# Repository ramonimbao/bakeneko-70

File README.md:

# Bakeneko 70 V1

A 70% keyboard based on the Bakeneko 60 by kkatano.

## Notes

Since this was based off of the Bakeneko 60, please take note that some files might still be named as bakeneko-60 or such. 

## Layouts

---

# Bakeneko 60 V3

A simple 60% keyboard for DIYers. This project is a special homage to TGR x Singa UNIKORN 60 and OTD 356 Mini.

## Features

- Single piece tray case
- O-ring gasket mount (Friction fit)
- USB-C with [Unified Daughterboard](https://github.com/ai03-2725/Unified-Daughterboard)
- QMK firmware and VIA ready
- Compatible with common 60% plates

## Specs

- Dimensions: 295 x 110 x 30mm
- Front height: 18.5mm
- Home row height: 31mm(with GMK keycaps and bumpons)
- Typing angle: 6 degree
- Weight:
  - PLA Case: 370g
  - Aluminum Case: 700g
- O-ring gasket: VMQ-50(Silicone 50 duro) AS568-262

## Notes

- All files are to be used at your own risk
- As for stabilizers, only PCB snap ins are supported
- This open source version is not compatible with CannonKeys' Bakeneko

## Resources

- Documents: https://drive.google.com/drive/folders/1tddSihOS8Pgf1lTQOjHohYCl8efxXIeH
  - Parts guide and other useful information
  - Will be added and updated as needed
- Discord: https://discord.gg/fMY96TeEwV
  - Have fun with community members
  - Talk about Bakeneko builds and mods, and share your works
  - You can also contact me from there

## Special thanks to

- **Elaine** for [Unikorn](https://geekhack.org/index.php?topic=98587.50). Allowed me to publish the Unikorn-inspired case as open source and encouraged me
- Of course, I also show my respect and gratitude to **yuktsi**
- **coarse** for PCB review and kind support. His great work has refined the PCB well

## Also I should mention

- **OTD** for 356 Mini. Origin of O-ring gasket mount style
- **Evy** for [Plain60 series](https://github.com/evyd13/plain60-c). I used it as a reference for my PCB design. They also answered my miscellaneous questions
- **ai03** for [MX_Alps_Hybrid](https://github.com/ai03-2725/MX_Alps_Hybrid) and [random-keyboard-parts.pretty](https://github.com/ai03-2725/random-keyboard-parts.pretty). Also got a lot of help from his discord server
- **overset** for [JP01](https://github.com/overset/JP01). The idea of publishing the case design on Onshape. After seeing their great work I switched from fusion360 to Onshape
- **Rhuk** gave me a lot of advice on keyboard design and manufacturing
- **Maker Keyboards** suggested adding a plate cutout to remove the PCB using a keycap puller
- And many community members for giving me advice and feedback, thanks!

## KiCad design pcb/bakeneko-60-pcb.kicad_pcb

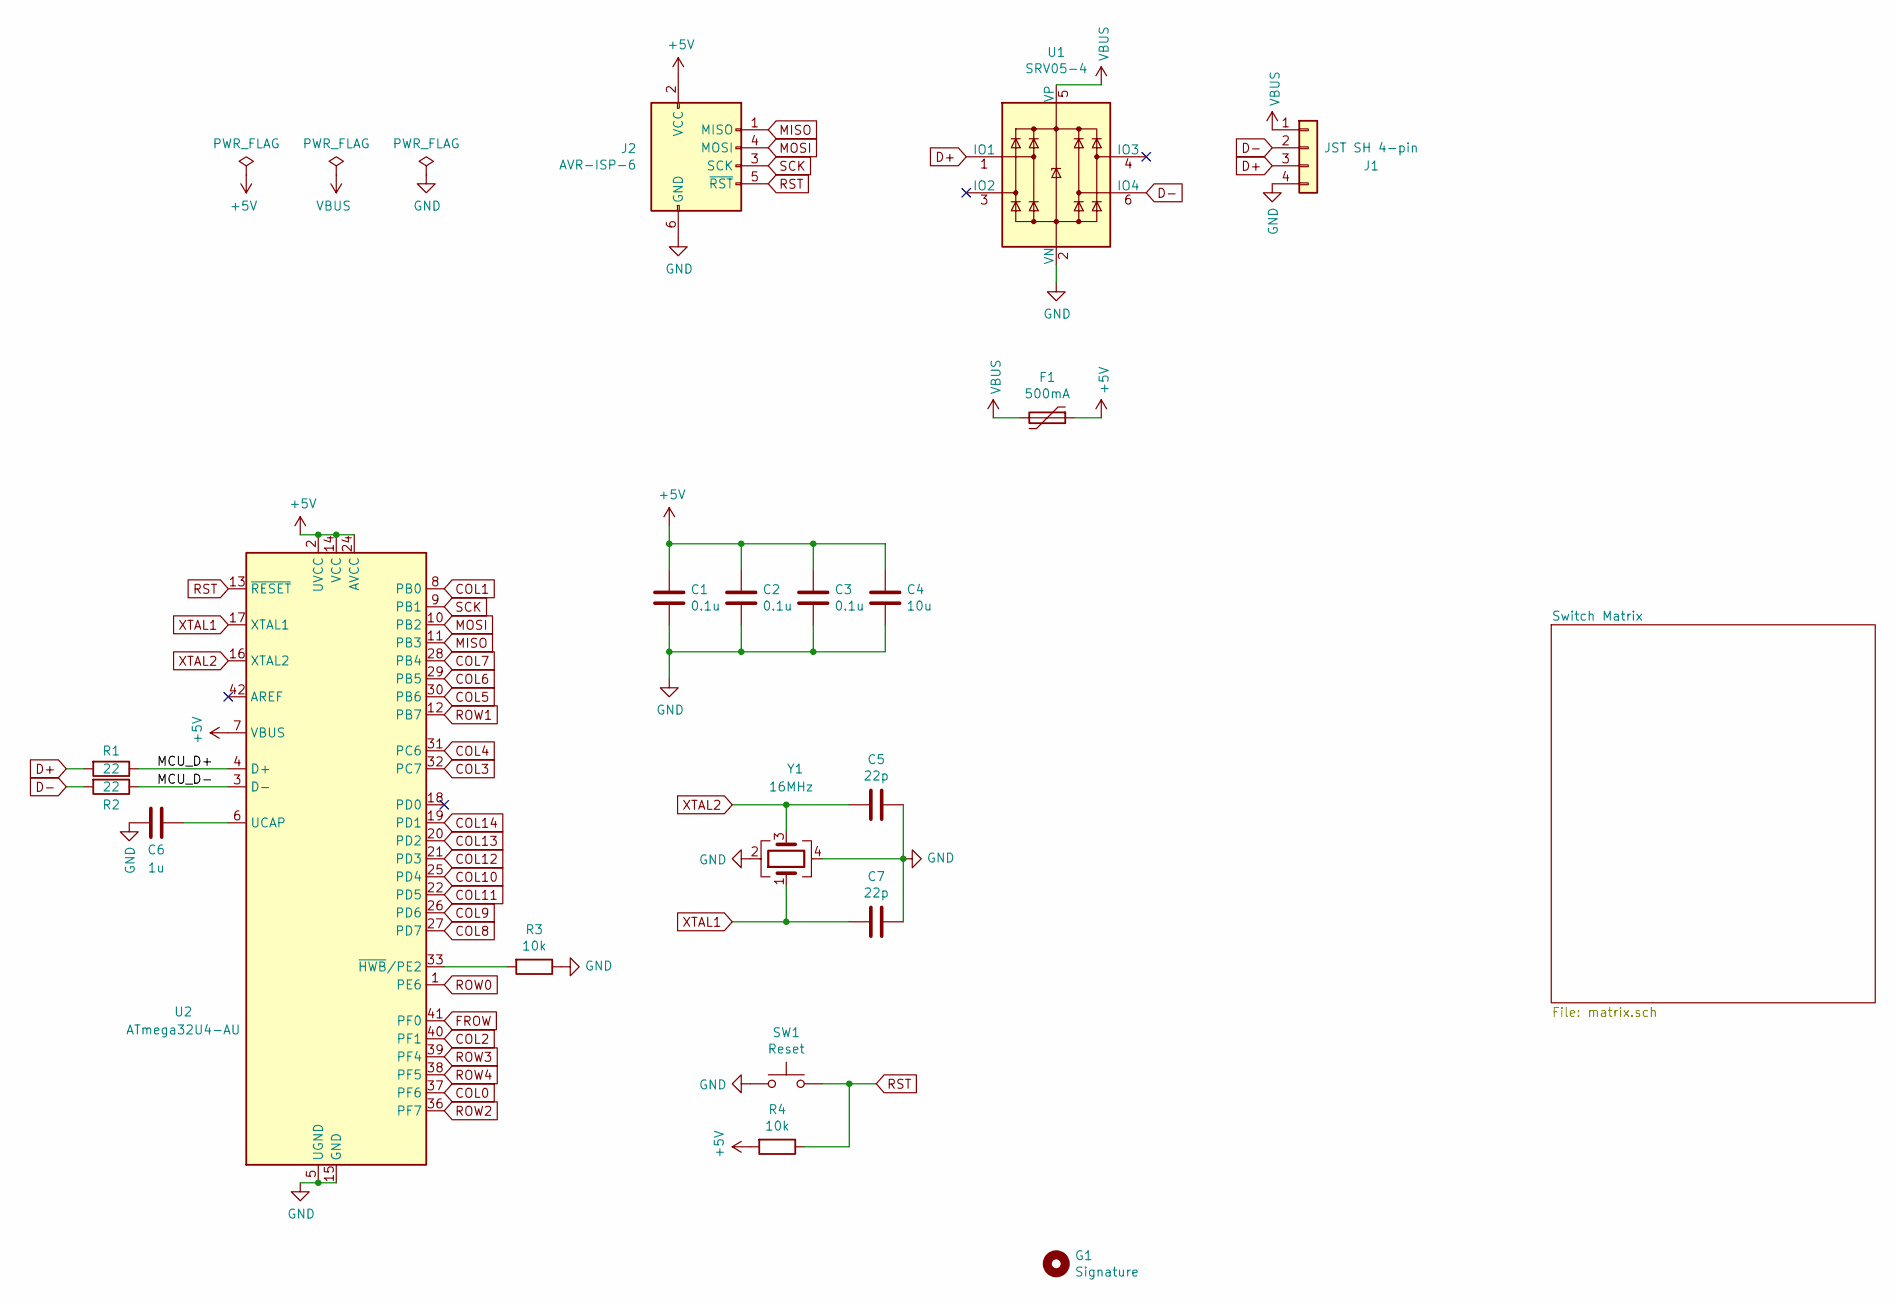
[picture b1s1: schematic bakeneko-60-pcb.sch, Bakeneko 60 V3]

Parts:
C1, C2, C3: 0.1u; C_0805_2012Metric; LCSC Part # C49678
C4: 10u; C_0805_2012Metric; LCSC Part # C15850
C5, C7: 22p; C_0805_2012Metric; LCSC Part # C1804
C6: 1u; C_0805_2012Metric; LCSC Part # C28323
F1: 500mA; Fuse_1206_3216Metric; LCSC Part # C70076
G1: Signature
J1: JST SH 4-pin; JST_SH_SM04B-SRSS-TB_1x04-1MP_P1.00mm_Horizontal; LCSC Part # C160404
J2: AVR-ISP-6; Reset_Pretty
R1, R2: 22; R_0805_2012Metric; LCSC Part # C17561
R3, R4: 10k; R_0805_2012Metric; LCSC Part # C17414
SW1: Reset; SW_SPST_TL3342; LCSC Part # C318884
U1: SRV05-4; SOT-23-6; LCSC Part # C85364
U2: ATmega32U4-AU; TQFP-44_10x10mm_P0.8mm; LCSC Part # C44854
Y1: 16MHz; Crystal_SMD_3225-4Pin_3.2x2.5mm; LCSC Part # C13738

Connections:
+5V: C1.1, C2.1, C3.1, C4.1, F1.1, J2.2 (VCC), R4.2, U2.2 (UVCC), U2.7 (VBUS), U2.14 (VCC), U2.24 (AVCC), U2.34 (VCC), U2.44 (AVCC)
/MCU_D+: R1.1, U2.4 (D+)
/MCU_D-: R2.1, U2.3 (D-)
COL0: U2.37 (PF6); also elsewhere on the board
COL1: U2.8 (PB0); also elsewhere on the board
COL2: U2.40 (PF1); also elsewhere on the board
COL3: U2.32 (PC7); also elsewhere on the board
COL4: U2.31 (PC6); also elsewhere on the board
COL5: U2.30 (PB6); also elsewhere on the board
COL6: U2.29 (PB5); also elsewhere on the board
COL7: U2.28 (PB4); also elsewhere on the board
COL8: U2.27 (PD7); also elsewhere on the board
COL9: U2.26 (PD6); also elsewhere on the board
COL10: U2.25 (PD4); also elsewhere on the board
COL11: U2.22 (PD5); also elsewhere on the board
COL12: U2.21 (PD3); also elsewhere on the board
COL13: U2.20 (PD2); also elsewhere on the board
COL14: U2.19 (PD1); also elsewhere on the board
D+: J1.3, R1.2, U1.1 (IO1)
D-: J1.2, R2.2, U1.6 (IO4)
FROW: U2.41 (PF0); also elsewhere on the board
GND: C1.2, C2.2, C3.2, C4.2, C5.1, C6.2, C7.1, J1.4, J2.6 (GND), R3.1, SW1.1, U1.2 (VN), U2.5 (UGND), U2.15 (GND), U2.23 (GND), U2.35 (GND), U2.43 (GND), Y1.2, Y1.4
MISO: J2.1 (MISO), U2.11 (PB3)
MOSI: J2.4 (MOSI), U2.10 (PB2)
unnamed: C6.1, U2.6 (UCAP)
unnamed: R3.2, U2.33 (~HWB~/PE2)
ROW0: U2.1 (PE6); also elsewhere on the board
ROW1: U2.12 (PB7); also elsewhere on the board
ROW2: U2.36 (PF7); also elsewhere on the board
ROW3: U2.39 (PF4); also elsewhere on the board
ROW4: U2.38 (PF5); also elsewhere on the board
RST: J2.5 (~RST), R4.1, SW1.2, U2.13 (~RESET)
SCK: J2.3 (SCK), U2.9 (PB1)
VBUS: F1.2, J1.1, U1.5 (VP)
XTAL1: C7.2, U2.17 (XTAL1), Y1.1
XTAL2: C5.2, U2.16 (XTAL2), Y1.3

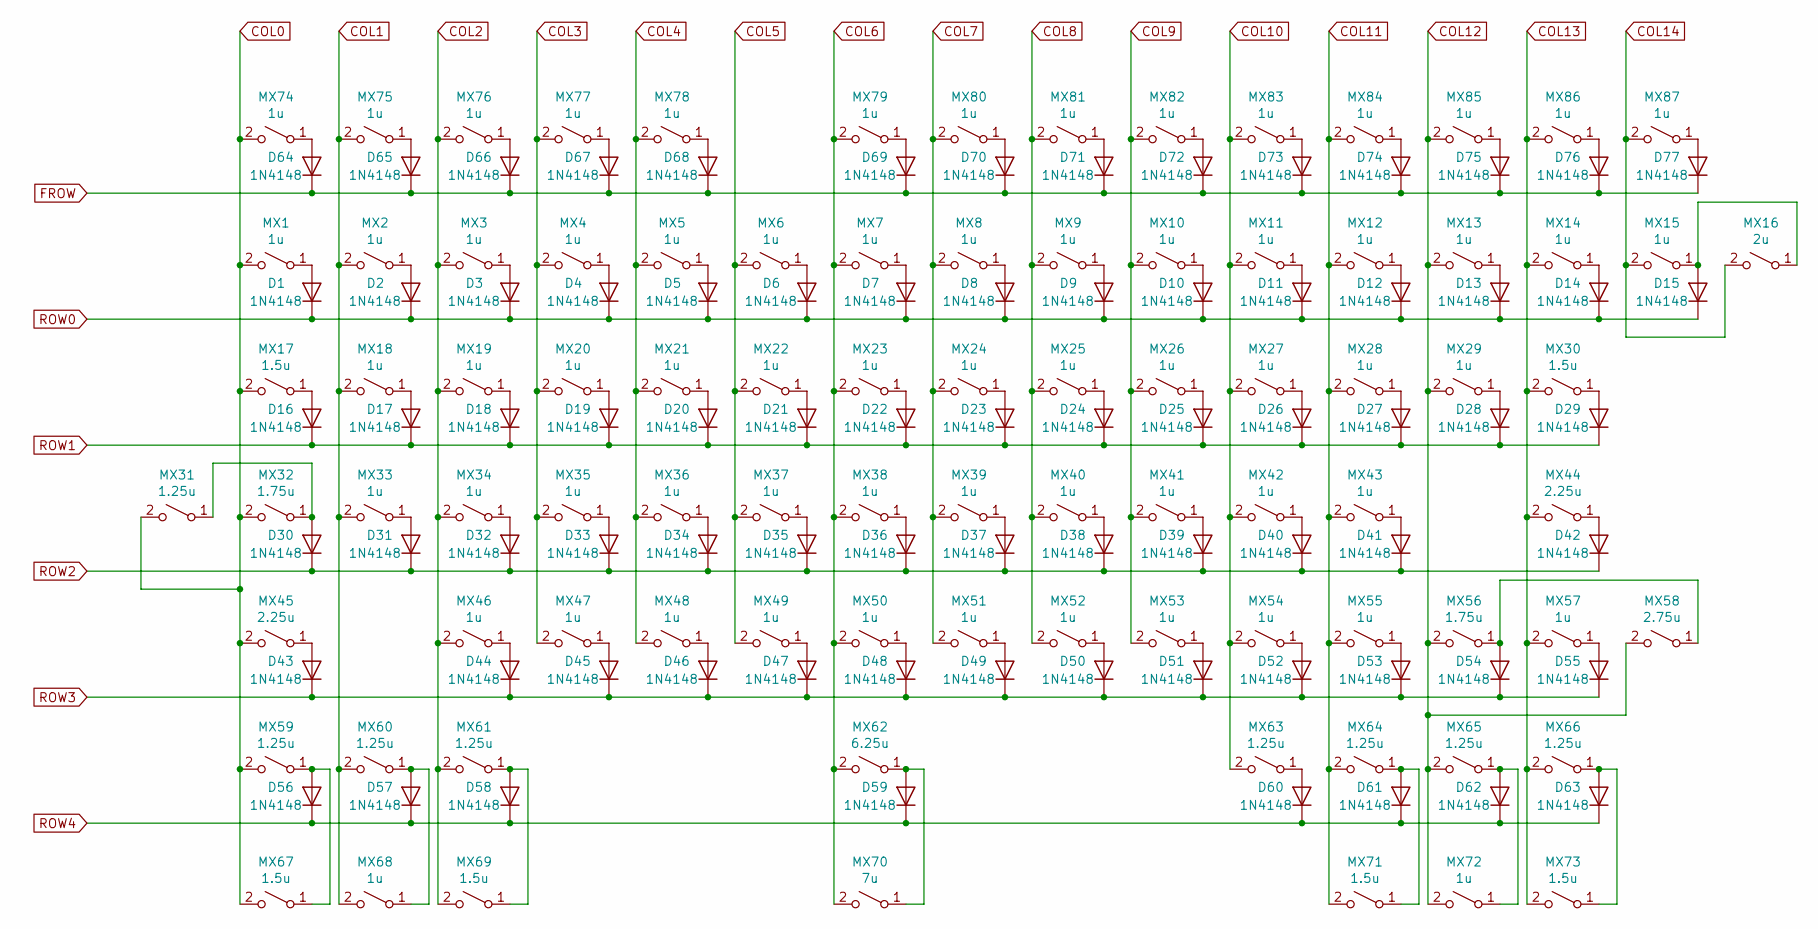
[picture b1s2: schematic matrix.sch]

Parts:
D1, D2, D3, D4, D5, D6, D7, D8, D9, D10, D11, D12, D13, D14, D15, D16, D17, D18, D19, D20, D21, D22, D23, D24, D25, D26, D27, D28, D29, D30, D31, D32, D33, D34, D35, D36, D37, D38, D39, D40, D41, D42, D43, D44, D45, D46, D47, D48, D49, D50, D51, D52, D53, D54, D55, D56, D57, D58, D59, D60, D61, D62, D63, D64, D65, D66, D67, D68, D69, D70, D71, D72, D73, D74, D75, D76, D77: 1N4148; D_SOD-123; LCSC Part # C81598
MX1, MX2, MX3, MX4, MX5, MX6, MX7, MX8, MX9, MX10, MX11, MX12, MX13, MX14, MX15, MX18, MX19, MX20, MX21, MX22, MX23, MX24, MX25, MX26, MX27, MX28, MX29, MX33, MX34, MX35, MX36, MX37, MX38, MX39, MX40, MX41, MX42, MX43, MX46, MX47, MX48, MX49, MX50, MX51, MX52, MX53, MX54, MX55, MX57, MX68, MX72, MX74, MX75, MX76, MX77, MX78, MX79, MX80, MX81, MX82, MX83, MX84, MX85, MX86, MX87: 1u; MXOnly-1U-NoLED
MX16: 2u; MXOnly-2U-NoLED
MX17, MX30, MX67, MX69, MX71, MX73: 1.5u; MXOnly-1.5U-NoLED
MX31, MX59, MX60, MX61, MX63, MX64, MX65, MX66: 1.25u; MXOnly-1.25U-NoLED
MX32, MX56: 1.75u; MXOnly-1.75U-NoLED
MX44, MX45: 2.25u; MXOnly-2.25U-NoLED
MX58: 2.75u; MXOnly-2.75U-NoLED
MX62: 6.25u; MXOnly-6.25U-ReversedStabilizers-NoLED
MX70: 7u; MXOnly-7U-ReversedStabilizers-NoLED

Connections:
COL0: MX1.2 (B), MX17.2 (B), MX31.2 (B), MX32.2 (B), MX45.2 (B), MX59.2 (B), MX67.2 (B), MX74.2 (B); also elsewhere on the board
COL1: MX2.2 (B), MX18.2 (B), MX33.2 (B), MX60.2 (B), MX68.2 (B), MX75.2 (B); also elsewhere on the board
COL2: MX3.2 (B), MX19.2 (B), MX34.2 (B), MX46.2 (B), MX61.2 (B), MX69.2 (B), MX76.2 (B); also elsewhere on the board
COL3: MX4.2 (B), MX20.2 (B), MX35.2 (B), MX47.2 (B), MX77.2 (B); also elsewhere on the board
COL4: MX5.2 (B), MX21.2 (B), MX36.2 (B), MX48.2 (B), MX78.2 (B); also elsewhere on the board
COL5: MX6.2 (B), MX22.2 (B), MX37.2 (B), MX49.2 (B); also elsewhere on the board
COL6: MX7.2 (B), MX23.2 (B), MX38.2 (B), MX50.2 (B), MX62.2 (B), MX70.2 (B), MX79.2 (B); also elsewhere on the board
COL7: MX8.2 (B), MX24.2 (B), MX39.2 (B), MX51.2 (B), MX80.2 (B); also elsewhere on the board
COL8: MX9.2 (B), MX25.2 (B), MX40.2 (B), MX52.2 (B), MX81.2 (B); also elsewhere on the board
COL9: MX10.2 (B), MX26.2 (B), MX41.2 (B), MX53.2 (B), MX82.2 (B); also elsewhere on the board
COL10: MX11.2 (B), MX27.2 (B), MX42.2 (B), MX54.2 (B), MX63.2 (B), MX83.2 (B); also elsewhere on the board
COL11: MX12.2 (B), MX28.2 (B), MX43.2 (B), MX55.2 (B), MX64.2 (B), MX71.2 (B), MX84.2 (B); also elsewhere on the board
COL12: MX13.2 (B), MX29.2 (B), MX56.2 (B), MX58.2 (B), MX65.2 (B), MX72.2 (B), MX85.2 (B); also elsewhere on the board
COL13: MX14.2 (B), MX30.2 (B), MX44.2 (B), MX57.2 (B), MX66.2 (B), MX73.2 (B), MX86.2 (B); also elsewhere on the board
COL14: MX15.2 (B), MX16.2 (B), MX87.2 (B); also elsewhere on the board
FROW: D64.1 (K), D65.1 (K), D66.1 (K), D67.1 (K), D68.1 (K), D69.1 (K), D70.1 (K), D71.1 (K), D72.1 (K), D73.1 (K), D74.1 (K), D75.1 (K), D76.1 (K), D77.1 (K); also elsewhere on the board
unnamed: D1.2 (A), MX1.1 (A)
unnamed: D2.2 (A), MX2.1 (A)
unnamed: D3.2 (A), MX3.1 (A)
unnamed: D4.2 (A), MX4.1 (A)
unnamed: D5.2 (A), MX5.1 (A)
unnamed: D6.2 (A), MX6.1 (A)
unnamed: D7.2 (A), MX7.1 (A)
unnamed: D8.2 (A), MX8.1 (A)
unnamed: D9.2 (A), MX9.1 (A)
unnamed: D10.2 (A), MX10.1 (A)
unnamed: D11.2 (A), MX11.1 (A)
unnamed: D12.2 (A), MX12.1 (A)
unnamed: D13.2 (A), MX13.1 (A)
unnamed: D14.2 (A), MX14.1 (A)
unnamed: D15.2 (A), MX15.1 (A), MX16.1 (A)
unnamed: D16.2 (A), MX17.1 (A)
unnamed: D17.2 (A), MX18.1 (A)
unnamed: D18.2 (A), MX19.1 (A)
unnamed: D19.2 (A), MX20.1 (A)
unnamed: D20.2 (A), MX21.1 (A)
unnamed: D21.2 (A), MX22.1 (A)
unnamed: D22.2 (A), MX23.1 (A)
unnamed: D23.2 (A), MX24.1 (A)
unnamed: D24.2 (A), MX25.1 (A)
unnamed: D25.2 (A), MX26.1 (A)
unnamed: D26.2 (A), MX27.1 (A)
unnamed: D27.2 (A), MX28.1 (A)
unnamed: D28.2 (A), MX29.1 (A)
unnamed: D29.2 (A), MX30.1 (A)
unnamed: D30.2 (A), MX31.1 (A), MX32.1 (A)
unnamed: D31.2 (A), MX33.1 (A)
unnamed: D32.2 (A), MX34.1 (A)
unnamed: D33.2 (A), MX35.1 (A)
unnamed: D34.2 (A), MX36.1 (A)
unnamed: D35.2 (A), MX37.1 (A)
unnamed: D36.2 (A), MX38.1 (A)
unnamed: D37.2 (A), MX39.1 (A)
unnamed: D38.2 (A), MX40.1 (A)
unnamed: D39.2 (A), MX41.1 (A)
unnamed: D40.2 (A), MX42.1 (A)
unnamed: D41.2 (A), MX43.1 (A)
unnamed: D42.2 (A), MX44.1 (A)
unnamed: D43.2 (A), MX45.1 (A)
unnamed: D44.2 (A), MX46.1 (A)
unnamed: D45.2 (A), MX47.1 (A)
unnamed: D46.2 (A), MX48.1 (A)
unnamed: D47.2 (A), MX49.1 (A)
unnamed: D48.2 (A), MX50.1 (A)
unnamed: D49.2 (A), MX51.1 (A)
unnamed: D50.2 (A), MX52.1 (A)
unnamed: D51.2 (A), MX53.1 (A)
unnamed: D52.2 (A), MX54.1 (A)
unnamed: D53.2 (A), MX55.1 (A)
unnamed: D54.2 (A), MX56.1 (A), MX58.1 (A)
unnamed: D55.2 (A), MX57.1 (A)
unnamed: D56.2 (A), MX59.1 (A), MX67.1 (A)
unnamed: D57.2 (A), MX60.1 (A), MX68.1 (A)
unnamed: D58.2 (A), MX61.1 (A), MX69.1 (A)
unnamed: D59.2 (A), MX62.1 (A), MX70.1 (A)
unnamed: D60.2 (A), MX63.1 (A)
unnamed: D61.2 (A), MX64.1 (A), MX71.1 (A)
unnamed: D62.2 (A), MX65.1 (A), MX72.1 (A)
unnamed: D63.2 (A), MX66.1 (A), MX73.1 (A)
unnamed: D64.2 (A), MX74.1 (A)
unnamed: D65.2 (A), MX75.1 (A)
unnamed: D66.2 (A), MX76.1 (A)
unnamed: D67.2 (A), MX77.1 (A)
unnamed: D68.2 (A), MX78.1 (A)
unnamed: D69.2 (A), MX79.1 (A)
unnamed: D70.2 (A), MX80.1 (A)
unnamed: D71.2 (A), MX81.1 (A)
unnamed: D72.2 (A), MX82.1 (A)
unnamed: D73.2 (A), MX83.1 (A)
unnamed: D74.2 (A), MX84.1 (A)
unnamed: D75.2 (A), MX85.1 (A)
unnamed: D76.2 (A), MX86.1 (A)
unnamed: D77.2 (A), MX87.1 (A)
ROW0: D1.1 (K), D2.1 (K), D3.1 (K), D4.1 (K), D5.1 (K), D6.1 (K), D7.1 (K), D8.1 (K), D9.1 (K), D10.1 (K), D11.1 (K), D12.1 (K), D13.1 (K), D14.1 (K), D15.1 (K); also elsewhere on the board
ROW1: D16.1 (K), D17.1 (K), D18.1 (K), D19.1 (K), D20.1 (K), D21.1 (K), D22.1 (K), D23.1 (K), D24.1 (K), D25.1 (K), D26.1 (K), D27.1 (K), D28.1 (K), D29.1 (K); also elsewhere on the board
ROW2: D30.1 (K), D31.1 (K), D32.1 (K), D33.1 (K), D34.1 (K), D35.1 (K), D36.1 (K), D37.1 (K), D38.1 (K), D39.1 (K), D40.1 (K), D41.1 (K), D42.1 (K); also elsewhere on the board
ROW3: D43.1 (K), D44.1 (K), D45.1 (K), D46.1 (K), D47.1 (K), D48.1 (K), D49.1 (K), D50.1 (K), D51.1 (K), D52.1 (K), D53.1 (K), D54.1 (K), D55.1 (K); also elsewhere on the board
ROW4: D56.1 (K), D57.1 (K), D58.1 (K), D59.1 (K), D60.1 (K), D61.1 (K), D62.1 (K), D63.1 (K); also elsewhere on the board

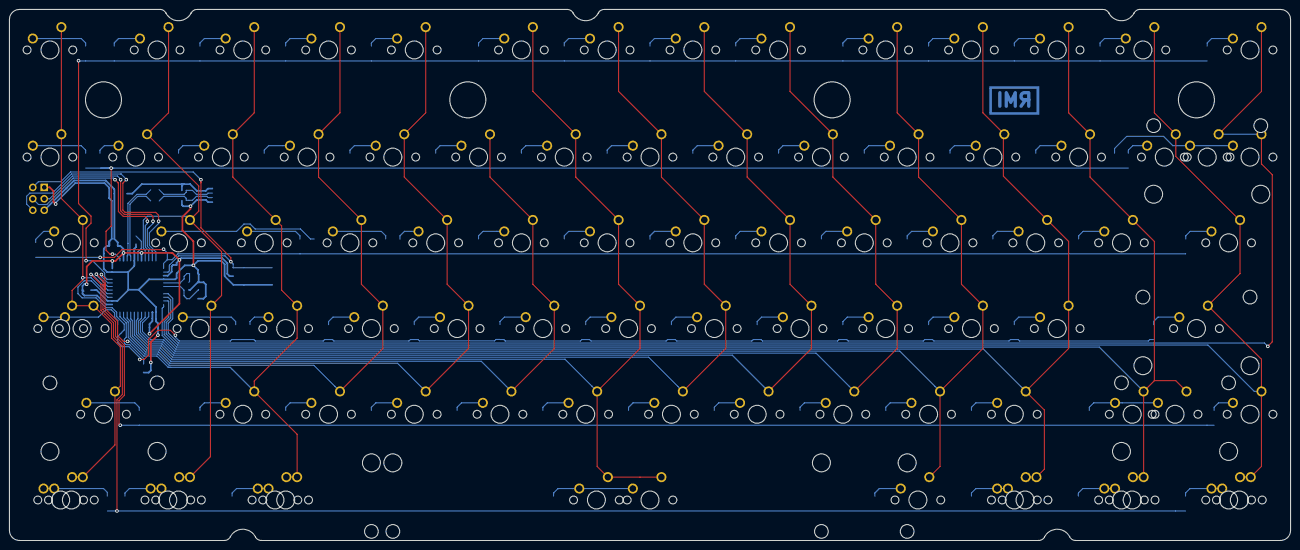
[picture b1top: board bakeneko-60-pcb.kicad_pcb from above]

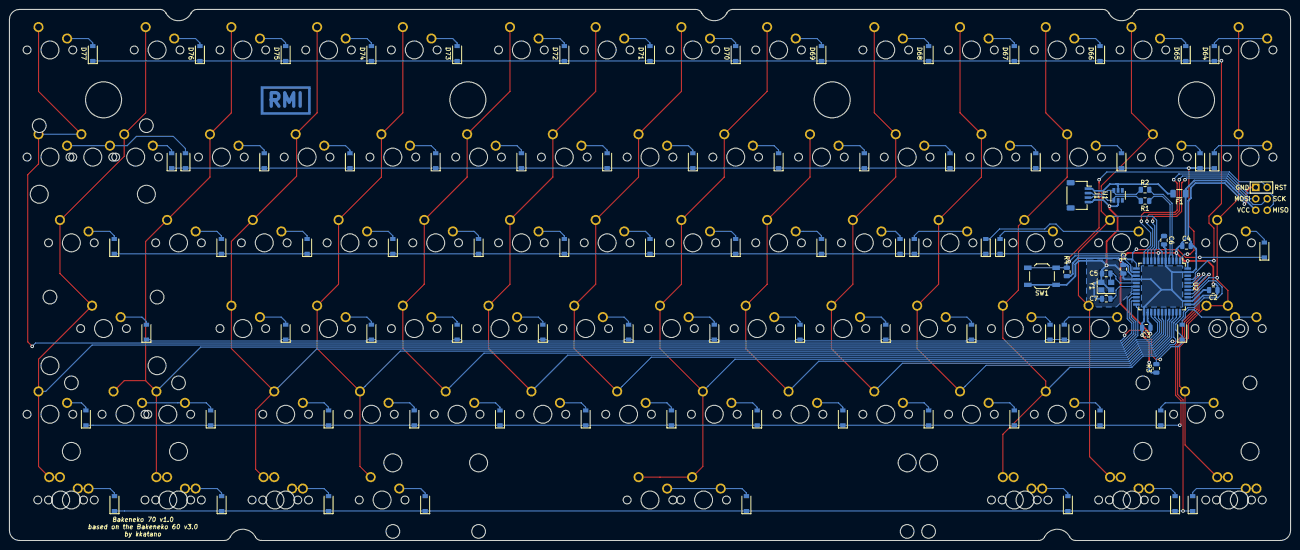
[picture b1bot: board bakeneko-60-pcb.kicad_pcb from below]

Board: 2 copper layers, 284.7 x 118.0 mm, 183 parts (96 on the bottom side), 113 nets.

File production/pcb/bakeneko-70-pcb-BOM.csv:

Comment,Designator,Footprint,LCSC
"0.1u","C1,C2,C3","Capacitor_SMD:C_0805_2012Metric",""
"10u","C4","Capacitor_SMD:C_0805_2012Metric",""
"22p","C5,C7","Capacitor_SMD:C_0805_2012Metric",""
"1u","C6","Capacitor_SMD:C_0805_2012Metric",""
"1N4148","D1,D2,D3,D4,D5,D6,D7,D8,D9,D10,D11,D12,D13,D14,D15,D16,D17,D18,D19,D20,D21,D22,D23,D24,D25,D26,D27,D28,D29,D30,D31,D32,D33,D34,D35,D36,D37,D38,D39,D40,D41,D42,D43,D44,D45,D46,D47,D48,D49,D50,D51,D52,D53,D54,D55,D56,D57,D58,D59,D60,D61,D62,D63,D64,D65,D66,D67,D68,D69,D70,D71,D72,D73,D74,D75,D76,D77","Diode_SMD:D_SOD-123",""
"500mA","F1","Fuse:Fuse_1206_3216Metric",""
"Signature","G1","Ramon:Signature",""
"JST SH 4-pin","J1","Connector_JST:JST_SH_SM04B-SRSS-TB_1x04-1MP_P1.00mm_Horizontal",""
"AVR-ISP-6","J2","random-keyboard-parts:Reset_Pretty",""
"2u","MX16","MX_Only:MXOnly-2U-NoLED",""
"1.5u","MX17,MX30,MX67,MX69,MX71,MX73","MX_Only:MXOnly-1.5U-NoLED",""
"1.25u","MX31,MX59,MX60,MX61,MX63,MX64,MX65,MX66","MX_Only:MXOnly-1.25U-NoLED",""
"1.75u","MX32,MX56","MX_Only:MXOnly-1.75U-NoLED",""
"2.25u","MX44,MX45","MX_Only:MXOnly-2.25U-NoLED",""
"1u","MX1,MX2,MX3,MX4,MX5,MX6,MX7,MX8,MX9,MX10,MX11,MX12,MX13,MX14,MX15,MX18,MX19,MX20,MX21,MX22,MX23,MX24,MX25,MX26,MX27,MX28,MX29,MX33,MX34,MX35,MX36,MX37,MX38,MX39,MX40,MX41,MX42,MX43,MX46,MX47,MX48,MX49,MX50,MX51,MX52,MX53,MX54,MX55,MX57,MX68,MX72,MX74,MX75,MX76,MX77,MX78,MX79,MX80,MX81,MX82,MX83,MX84,MX85,MX86,MX87","MX_Only:MXOnly-1U-NoLED",""
"2.75u","MX58","MX_Only:MXOnly-2.75U-NoLED",""
"6.25u","MX62","MX_Only:MXOnly-6.25U-ReversedStabilizers-NoLED",""
"7u","MX70","MX_Only:MXOnly-7U-ReversedStabilizers-NoLED",""
"22","R1,R2","Resistor_SMD:R_0805_2012Metric",""
"10k","R3,R4","Resistor_SMD:R_0805_2012Metric",""
"Reset","SW1","Button_Switch_SMD:SW_SPST_TL3342",""
"SRV05-4","U1","Package_TO_SOT_SMD:SOT-23-6",""
"ATmega32U4-AU","U2","Package_QFP:TQFP-44_10x10mm_P0.8mm",""
"16MHz","Y1","Crystal:Crystal_SMD_3225-4Pin_3.2x2.5mm",""

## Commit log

2021-11-10 Bakeneko-70 intial implementation
2022-01-09 Add bakeneko 70 files
2022-01-11 Update case step file
